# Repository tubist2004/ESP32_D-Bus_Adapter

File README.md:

# ESP32 D-Bus Adapter

This is a repository for building a (or more) ESP32 based D-Bus Adapter for BSH appliances.

It is based on the awesome work of [@hn](https://github.com/hn) who did reverse engineering of the protocol, wrote some software and most important: Talked about it!

Please follow his project: https://github.com/hn/bsh-home-appliances

And see his talk at the 39C3: https://media.ccc.de/v/39c3-hacking-washing-machines

---

<a href="https://github.com/tubist2004/ESP32_D-Bus_Adapter">ESP32_D-Bus_Adapter</a> © 2026 by <a href="https://example.com">tubist2004</a> is licensed under <a href="https://creativecommons.org/licenses/by/4.0/">CC BY 4.0</a>

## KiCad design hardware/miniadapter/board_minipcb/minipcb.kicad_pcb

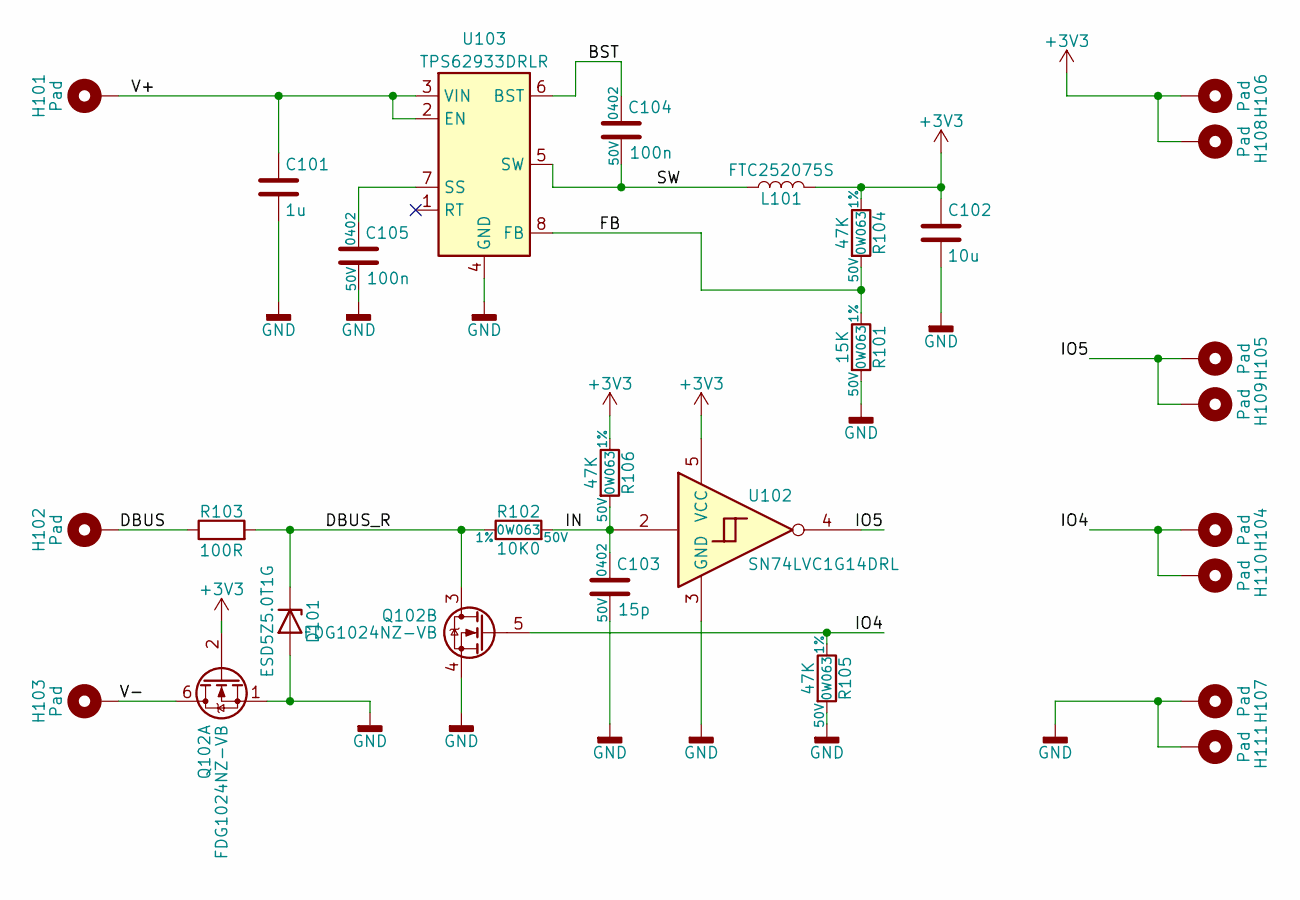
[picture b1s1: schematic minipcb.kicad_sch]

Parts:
C101: 1u; C_0603_1608Metric
C102: 10u; C_0603_1608Metric
C103: C_15p_0402_NP0_5%_50V; C_0402_1005Metric; Tolerance 5%; Voltage 50V
C104, C105: C_100n_0402_X7R_10%_50V; C_0402_1005Metric; Tolerance 10%; Voltage 50V
D101: ESD5Z5.0T1G; D_SOD-523
H101, H102, H103: Pad; TE_2040852-1
H104, H105, H106, H107, H108, H109, H110, H111: Pad; SolderWirePad_1x01_SMD_1.5x3mm
L101: FTC252075S; L_Changjiang_FTC252075S
Q102: FDG1024NZ-VB; SOT-363_SC-70-6
R101: R_15K_0402_0W063_1%_100PPM_50V; R_0402_1005Metric; Tolerance 1%; Voltage 50V
R102: R_10K0_0402_0W063_1%_100PPM_50V; R_0402_1005Metric; Tolerance 1%; Voltage 50V
R103: 100R; R_0603_1608Metric
R104, R105, R106: R_47K_0402_0W063_1%_100PPM_50V; R_0402_1005Metric; Tolerance 1%; Voltage 50V
U102: SN74LVC1G14DRL; SOT-553
U103: TPS62933DRLR; SOT-583-8

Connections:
+3V3: C102.1, H106.1, H108.1, L101.2, Q102.2 (G), R104.1, R106.1, U102.5 (VCC)
/BST: C104.1, U103.6 (BST)
/DBUS: H102.1, R103.1
/DBUS_R: D101.1 (K), Q102.3 (D), R102.1, R103.2
/FB: R101.1, R104.2, U103.8 (FB)
/IN: C103.1, R102.2, R106.2, U102.2
/IO4: H104.1, H110.1, Q102.5 (G), R105.1
/IO5: H105.1, H109.1, U102.4
/SW: C104.2, L101.1, U103.5 (SW)
/V+: C101.1, H101.1, U103.2 (EN), U103.3 (VIN)
/V-: H103.1, Q102.6 (D)
GND: C101.2, C102.2, C103.2, C105.2, D101.2 (A), H107.1, H111.1, Q102.1 (S), Q102.4 (S), R101.2, R105.2, U102.3 (GND), U103.4 (GND)
unnamed: C105.1, U103.7 (SS)

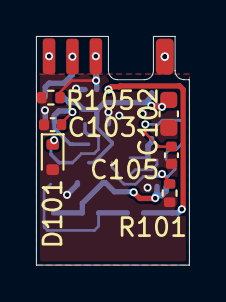
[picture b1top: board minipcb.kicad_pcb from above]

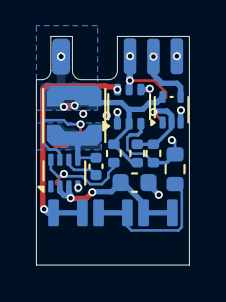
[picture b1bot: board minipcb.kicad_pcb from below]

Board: 2 copper layers, 8.5 x 12.7 mm, 27 parts (17 on the bottom side), 13 nets.

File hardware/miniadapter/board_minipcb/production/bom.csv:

Designator,Footprint,Quantity,Value,LCSC Part #
C101,0603,1,1u,
C102,0603,1,10u,
C103,0402,1,C_15p_0402_NP0_5%_50V,
"C104, C105",0402,2,C_100n_0402_X7R_10%_50V,
D101,D_SOD-523,1,ESD5Z5.0T1G,
"H101, H102, H103",TE_2040852-1,3,Pad,
L101,L_Coilcraft_LPS3010,1,FTC252075S,
Q102,SOT-363_SC-70-6,1,FDG1024NZ-VB,
R101,0402,1,R_15K_0402_0W063_1%_100PPM_50V,
R102,0402,1,R_10K0_0402_0W063_1%_100PPM_50V,
R103,0603,1,100R,
"R104, R105, R106",0402,3,R_47K_0402_0W063_1%_100PPM_50V,
U102,SOT-553,1,SN74LVC1G14DRL,
U103,SOT-583-8,1,TPS62933DRLR,

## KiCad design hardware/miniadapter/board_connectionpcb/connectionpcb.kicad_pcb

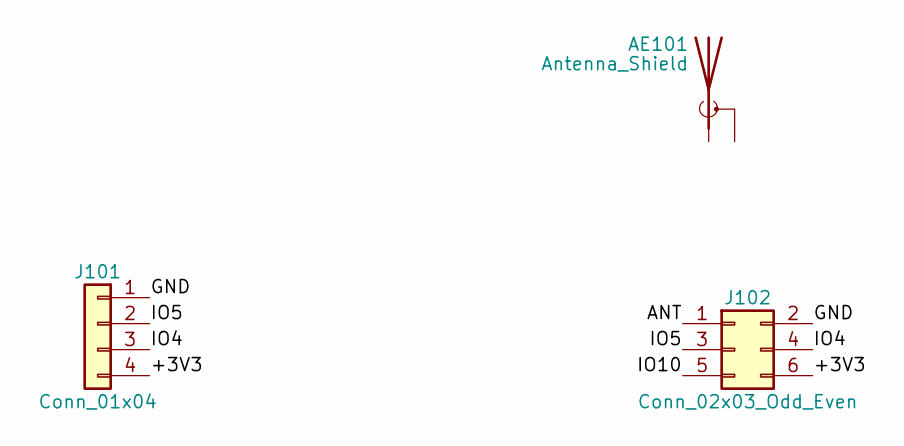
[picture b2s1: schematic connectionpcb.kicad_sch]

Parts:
AE101: Antenna_Shield; Johanson_2450AT18x100_2400-2500Mhz
J101: Conn_01x04; minipcb_alt_boardedge
J102: Conn_02x03_Odd_Even; ESP8685-WROOM-07

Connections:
/+3V3: J101.4, J102.6
/ANT: J102.1
/GND: J101.1, J102.2
/IO4: J101.3, J102.4
/IO5: J101.2, J102.3
/IO10: J102.5

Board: 2 copper layers, 3 parts (1 on the bottom side), 4 nets.

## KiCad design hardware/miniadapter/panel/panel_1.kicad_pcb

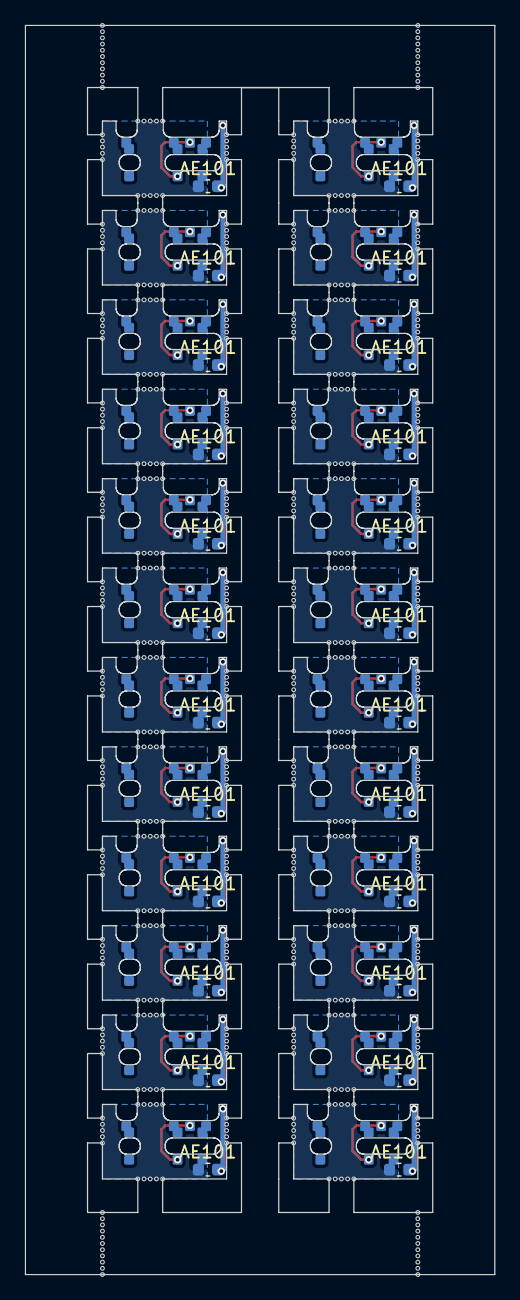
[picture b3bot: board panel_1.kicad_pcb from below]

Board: 2 copper layers, 37.8 x 100.6 mm, 596 parts (24 on the bottom side), 96 nets.

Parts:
AE101, AE101#2, AE101#3, AE101#4, AE101#5, AE101#6, AE101#7, AE101#8, AE101#9, AE101#10, AE101#11, AE101#12, AE101#13, AE101#14, AE101#15, AE101#16, AE101#17, AE101#18, AE101#19, AE101#20, AE101#21, AE101#22, AE101#23, AE101#24: Antenna_Shield; C_0603_1608Metric
J101, J101#2, J101#3, J101#4, J101#5, J101#6, J101#7, J101#8, J101#9, J101#10, J101#11, J101#12, J101#13, J101#14, J101#15, J101#16, J101#17, J101#18, J101#19, J101#20, J101#21, J101#22, J101#23, J101#24: Conn_01x04; minipcb_alt_boardedge
J102, J102#2, J102#3, J102#4, J102#5, J102#6, J102#7, J102#8, J102#9, J102#10, J102#11, J102#12, J102#13, J102#14, J102#15, J102#16, J102#17, J102#18, J102#19, J102#20, J102#21, J102#22, J102#23, J102#24: Conn_02x03_Odd_Even; ESP8685-WROOM-07
KiKit_MB_1_1, KiKit_MB_1_2, KiKit_MB_1_3, KiKit_MB_1_4, KiKit_MB_1_5, KiKit_MB_2_1, KiKit_MB_2_2, KiKit_MB_2_3, KiKit_MB_2_4, KiKit_MB_2_5, KiKit_MB_3_1, KiKit_MB_3_2, KiKit_MB_3_3, KiKit_MB_3_4, KiKit_MB_3_5, KiKit_MB_4_1, KiKit_MB_4_2, KiKit_MB_4_3, KiKit_MB_4_4, KiKit_MB_4_5, KiKit_MB_5_1, KiKit_MB_5_2, KiKit_MB_5_3, KiKit_MB_5_4, KiKit_MB_5_5, KiKit_MB_6_1, KiKit_MB_6_2, KiKit_MB_6_3, KiKit_MB_6_4, KiKit_MB_6_5, KiKit_MB_7_1, KiKit_MB_7_2, KiKit_MB_7_3, KiKit_MB_7_4, KiKit_MB_7_5, KiKit_MB_8_1, KiKit_MB_8_2, KiKit_MB_8_3, KiKit_MB_8_4, KiKit_MB_8_5, KiKit_MB_9_1, KiKit_MB_9_2, KiKit_MB_9_3, KiKit_MB_9_4, KiKit_MB_9_5, KiKit_MB_10_1, KiKit_MB_10_2, KiKit_MB_10_3, KiKit_MB_10_4, KiKit_MB_10_5, KiKit_MB_11_1, KiKit_MB_11_2, KiKit_MB_11_3, KiKit_MB_11_4, KiKit_MB_11_5, KiKit_MB_12_1, KiKit_MB_12_2, KiKit_MB_12_3, KiKit_MB_12_4, KiKit_MB_12_5, KiKit_MB_13_1, KiKit_MB_13_2, KiKit_MB_13_3, KiKit_MB_13_4, KiKit_MB_13_5, KiKit_MB_14_1, KiKit_MB_14_2, KiKit_MB_14_3, KiKit_MB_14_4, KiKit_MB_14_5, KiKit_MB_15_1, KiKit_MB_15_2, KiKit_MB_15_3, KiKit_MB_15_4, KiKit_MB_15_5, KiKit_MB_16_1, KiKit_MB_16_2, KiKit_MB_16_3, KiKit_MB_16_4, KiKit_MB_16_5, KiKit_MB_17_1, KiKit_MB_17_2, KiKit_MB_17_3, KiKit_MB_17_4, KiKit_MB_17_5, KiKit_MB_18_1, KiKit_MB_18_2, KiKit_MB_18_3, KiKit_MB_18_4, KiKit_MB_18_5, KiKit_MB_19_1, KiKit_MB_19_2, KiKit_MB_19_3, KiKit_MB_19_4, KiKit_MB_19_5, KiKit_MB_20_1, KiKit_MB_20_2, KiKit_MB_20_3, KiKit_MB_20_4, KiKit_MB_20_5, KiKit_MB_21_1, KiKit_MB_21_2, KiKit_MB_21_3, KiKit_MB_21_4, KiKit_MB_21_5, KiKit_MB_22_1, KiKit_MB_22_2, KiKit_MB_22_3, KiKit_MB_22_4, KiKit_MB_22_5, KiKit_MB_23_1, KiKit_MB_23_2, KiKit_MB_23_3, KiKit_MB_23_4, KiKit_MB_23_5, KiKit_MB_24_1, KiKit_MB_24_2, KiKit_MB_24_3, KiKit_MB_24_4, KiKit_MB_24_5, KiKit_MB_25_1, KiKit_MB_25_2, KiKit_MB_25_3, KiKit_MB_25_4, KiKit_MB_25_5, KiKit_MB_26_1, KiKit_MB_26_2, KiKit_MB_26_3, KiKit_MB_26_4, KiKit_MB_26_5, KiKit_MB_27_1, KiKit_MB_27_2, KiKit_MB_27_3, KiKit_MB_27_4, KiKit_MB_27_5, KiKit_MB_28_1, KiKit_MB_28_2, KiKit_MB_28_3, KiKit_MB_28_4, KiKit_MB_28_5, KiKit_MB_29_1, KiKit_MB_29_2, KiKit_MB_29_3, KiKit_MB_29_4, KiKit_MB_29_5, KiKit_MB_30_1, KiKit_MB_30_2, KiKit_MB_30_3, KiKit_MB_30_4, KiKit_MB_30_5, KiKit_MB_31_1, KiKit_MB_31_2, KiKit_MB_31_3, KiKit_MB_31_4, KiKit_MB_31_5, KiKit_MB_32_1, KiKit_MB_32_2, KiKit_MB_32_3, KiKit_MB_32_4, KiKit_MB_32_5, KiKit_MB_33_1, KiKit_MB_33_2, KiKit_MB_33_3, KiKit_MB_33_4, KiKit_MB_33_5, KiKit_MB_34_1, KiKit_MB_34_2, KiKit_MB_34_3, KiKit_MB_34_4, KiKit_MB_34_5, KiKit_MB_35_1, KiKit_MB_35_2, KiKit_MB_35_3, KiKit_MB_35_4, KiKit_MB_35_5, KiKit_MB_36_1, KiKit_MB_36_2, KiKit_MB_36_3, KiKit_MB_36_4, KiKit_MB_36_5, KiKit_MB_37_1, KiKit_MB_37_2, KiKit_MB_37_3, KiKit_MB_37_4, KiKit_MB_37_5, KiKit_MB_38_1, KiKit_MB_38_2, KiKit_MB_38_3, KiKit_MB_38_4, KiKit_MB_38_5, KiKit_MB_39_1, KiKit_MB_39_2, KiKit_MB_39_3, KiKit_MB_39_4, KiKit_MB_39_5, KiKit_MB_40_1, KiKit_MB_40_2, KiKit_MB_40_3, KiKit_MB_40_4, KiKit_MB_40_5, KiKit_MB_41_1, KiKit_MB_41_2, KiKit_MB_41_3, KiKit_MB_41_4, KiKit_MB_41_5, KiKit_MB_42_1, KiKit_MB_42_2, KiKit_MB_42_3, KiKit_MB_42_4, KiKit_MB_42_5, KiKit_MB_43_1, KiKit_MB_43_2, KiKit_MB_43_3, KiKit_MB_43_4, KiKit_MB_43_5, KiKit_MB_44_1, KiKit_MB_44_2, KiKit_MB_44_3, KiKit_MB_44_4, KiKit_MB_44_5, KiKit_MB_45_1, KiKit_MB_45_2, KiKit_MB_45_3, KiKit_MB_45_4, KiKit_MB_45_5, KiKit_MB_46_1, KiKit_MB_46_2, KiKit_MB_46_3, KiKit_MB_46_4, KiKit_MB_46_5, KiKit_MB_47_1, KiKit_MB_47_2, KiKit_MB_47_3, KiKit_MB_47_4, KiKit_MB_47_5, KiKit_MB_48_1, KiKit_MB_48_2, KiKit_MB_48_3, KiKit_MB_48_4, KiKit_MB_48_5, KiKit_MB_49_1, KiKit_MB_49_2, KiKit_MB_49_3, KiKit_MB_49_4, KiKit_MB_49_5, KiKit_MB_50_1, KiKit_MB_50_2, KiKit_MB_50_3, KiKit_MB_50_4, KiKit_MB_50_5, KiKit_MB_51_1, KiKit_MB_51_2, KiKit_MB_51_3, KiKit_MB_51_4, KiKit_MB_51_5, KiKit_MB_52_1, KiKit_MB_52_2, KiKit_MB_52_3, KiKit_MB_52_4, KiKit_MB_52_5, KiKit_MB_53_1, KiKit_MB_53_2, KiKit_MB_53_3, KiKit_MB_53_4, KiKit_MB_53_5, KiKit_MB_54_1, KiKit_MB_54_2, KiKit_MB_54_3, KiKit_MB_54_4, KiKit_MB_54_5, KiKit_MB_55_1, KiKit_MB_55_2, KiKit_MB_55_3, KiKit_MB_55_4, KiKit_MB_55_5, KiKit_MB_56_1, KiKit_MB_56_2, KiKit_MB_56_3, KiKit_MB_56_4, KiKit_MB_56_5, KiKit_MB_57_1, KiKit_MB_57_2, KiKit_MB_57_3, KiKit_MB_57_4, KiKit_MB_57_5, KiKit_MB_58_1, KiKit_MB_58_2, KiKit_MB_58_3, KiKit_MB_58_4, KiKit_MB_58_5, KiKit_MB_59_1, KiKit_MB_59_2, KiKit_MB_59_3, KiKit_MB_59_4, KiKit_MB_59_5, KiKit_MB_60_1, KiKit_MB_60_2, KiKit_MB_60_3, KiKit_MB_60_4, KiKit_MB_60_5, KiKit_MB_61_1, KiKit_MB_61_2, KiKit_MB_61_3, KiKit_MB_61_4, KiKit_MB_61_5, KiKit_MB_62_1, KiKit_MB_62_2, KiKit_MB_62_3, KiKit_MB_62_4, KiKit_MB_62_5, KiKit_MB_63_1, KiKit_MB_63_2, KiKit_MB_63_3, KiKit_MB_63_4, KiKit_MB_63_5, KiKit_MB_64_1, KiKit_MB_64_2, KiKit_MB_64_3, KiKit_MB_64_4, KiKit_MB_64_5, KiKit_MB_65_1, KiKit_MB_65_2, KiKit_MB_65_3, KiKit_MB_65_4, KiKit_MB_65_5, KiKit_MB_66_1, KiKit_MB_66_2, KiKit_MB_66_3, KiKit_MB_66_4, KiKit_MB_66_5, KiKit_MB_67_1, KiKit_MB_67_2, KiKit_MB_67_3, KiKit_MB_67_4, KiKit_MB_67_5, KiKit_MB_68_1, KiKit_MB_68_2, KiKit_MB_68_3, KiKit_MB_68_4, KiKit_MB_68_5, KiKit_MB_69_1, KiKit_MB_69_2, KiKit_MB_69_3, KiKit_MB_69_4, KiKit_MB_69_5, KiKit_MB_70_1, KiKit_MB_70_2, KiKit_MB_70_3, KiKit_MB_70_4, KiKit_MB_70_5, KiKit_MB_71_1, KiKit_MB_71_2, KiKit_MB_71_3, KiKit_MB_71_4, KiKit_MB_71_5, KiKit_MB_72_1, KiKit_MB_72_2, KiKit_MB_72_3, KiKit_MB_72_4, KiKit_MB_72_5, KiKit_MB_73_1, KiKit_MB_73_2, KiKit_MB_73_3, KiKit_MB_73_4, KiKit_MB_73_5, KiKit_MB_74_1, KiKit_MB_74_2, KiKit_MB_74_3, KiKit_MB_74_4, KiKit_MB_74_5, KiKit_MB_75_1, KiKit_MB_75_2, KiKit_MB_75_3, KiKit_MB_75_4, KiKit_MB_75_5, KiKit_MB_76_1, KiKit_MB_76_2, KiKit_MB_76_3, KiKit_MB_76_4, KiKit_MB_76_5, KiKit_MB_77_1, KiKit_MB_77_2, KiKit_MB_77_3, KiKit_MB_77_4, KiKit_MB_77_5, KiKit_MB_78_1, KiKit_MB_78_2, KiKit_MB_78_3, KiKit_MB_78_4, KiKit_MB_78_5, KiKit_MB_79_1, KiKit_MB_79_2, KiKit_MB_79_3, KiKit_MB_79_4, KiKit_MB_79_5, KiKit_MB_80_1, KiKit_MB_80_2, KiKit_MB_80_3, KiKit_MB_80_4, KiKit_MB_80_5, KiKit_MB_81_1, KiKit_MB_81_2, KiKit_MB_81_3, KiKit_MB_81_4, KiKit_MB_81_5, KiKit_MB_82_1, KiKit_MB_82_2, KiKit_MB_82_3, KiKit_MB_82_4, KiKit_MB_82_5, KiKit_MB_83_1, KiKit_MB_83_2, KiKit_MB_83_3, KiKit_MB_83_4, KiKit_MB_83_5, KiKit_MB_84_1, KiKit_MB_84_2, KiKit_MB_84_3, KiKit_MB_84_4, KiKit_MB_84_5, KiKit_MB_85_1, KiKit_MB_85_2, KiKit_MB_85_3, KiKit_MB_85_4, KiKit_MB_85_5, KiKit_MB_86_1, KiKit_MB_86_2, KiKit_MB_86_3, KiKit_MB_86_4, KiKit_MB_86_5, KiKit_MB_87_1, KiKit_MB_87_2, KiKit_MB_87_3, KiKit_MB_87_4, KiKit_MB_87_5, KiKit_MB_88_1, KiKit_MB_88_2, KiKit_MB_88_3, KiKit_MB_88_4, KiKit_MB_88_5, KiKit_MB_89_1, KiKit_MB_89_2, KiKit_MB_89_3, KiKit_MB_89_4, KiKit_MB_89_5, KiKit_MB_90_1, KiKit_MB_90_2, KiKit_MB_90_3, KiKit_MB_90_4, KiKit_MB_90_5, KiKit_MB_91_1, KiKit_MB_91_2, KiKit_MB_91_3, KiKit_MB_91_4, KiKit_MB_91_5, KiKit_MB_92_1, KiKit_MB_92_2, KiKit_MB_92_3, KiKit_MB_92_4, KiKit_MB_92_5, KiKit_MB_93_1, KiKit_MB_93_2, KiKit_MB_93_3, KiKit_MB_93_4, KiKit_MB_93_5, KiKit_MB_94_1, KiKit_MB_94_2, KiKit_MB_94_3, KiKit_MB_94_4, KiKit_MB_94_5, KiKit_MB_95_1, KiKit_MB_95_2, KiKit_MB_95_3, KiKit_MB_95_4, KiKit_MB_95_5, KiKit_MB_96_1, KiKit_MB_96_2, KiKit_MB_96_3, KiKit_MB_96_4, KiKit_MB_96_5, KiKit_MB_97_1, KiKit_MB_97_2, KiKit_MB_97_3, KiKit_MB_97_4, KiKit_MB_97_5, KiKit_MB_97_6, KiKit_MB_97_7, KiKit_MB_97_8, KiKit_MB_97_9, KiKit_MB_97_10, KiKit_MB_97_11, KiKit_MB_98_1, KiKit_MB_98_2, KiKit_MB_98_3, KiKit_MB_98_4, KiKit_MB_98_5, KiKit_MB_98_6, KiKit_MB_98_7, KiKit_MB_98_8, KiKit_MB_98_9, KiKit_MB_98_10, KiKit_MB_98_11, KiKit_MB_99_1, KiKit_MB_99_2, KiKit_MB_99_3, KiKit_MB_99_4, KiKit_MB_99_5, KiKit_MB_99_6, KiKit_MB_99_7, KiKit_MB_99_8, KiKit_MB_99_9, KiKit_MB_99_10, KiKit_MB_99_11, KiKit_MB_100_1, KiKit_MB_100_2, KiKit_MB_100_3, KiKit_MB_100_4, KiKit_MB_100_5, KiKit_MB_100_6, KiKit_MB_100_7, KiKit_MB_100_8, KiKit_MB_100_9, KiKit_MB_100_10, KiKit_MB_100_11: NPTH

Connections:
Board_0-/+3V3: J101#3.4, J102#4.6
Board_0-/GND: J101#3.1, J102#4.2
Board_0-/IO4: J101#3.3, J102#4.4
Board_0-/IO5: J101#3.2, J102#4.3
Board_1-/+3V3: J101#7.4, J102#3.6
Board_1-/GND: J101#7.1, J102#3.2
Board_1-/IO4: J101#7.3, J102#3.4
Board_1-/IO5: J101#7.2, J102#3.3
Board_2-/+3V3: J101#17.4, J102#18.6
Board_2-/GND: J101#17.1, J102#18.2
Board_2-/IO4: J101#17.3, J102#18.4
Board_2-/IO5: J101#17.2, J102#18.3
Board_3-/+3V3: J101#21.4, J102#5.6
Board_3-/GND: J101#21.1, J102#5.2
Board_3-/IO4: J101#21.3, J102#5.4
Board_3-/IO5: J101#21.2, J102#5.3
Board_4-/+3V3: J101#18.4, J102#21.6
Board_4-/GND: J101#18.1, J102#21.2
Board_4-/IO4: J101#18.3, J102#21.4
Board_4-/IO5: J101#18.2, J102#21.3
Board_5-/+3V3: J101#20.4, J102#7.6
Board_5-/GND: J101#20.1, J102#7.2
Board_5-/IO4: J101#20.3, J102#7.4
Board_5-/IO5: J101#20.2, J102#7.3
Board_6-/+3V3: J101#23.4, J102#13.6
Board_6-/GND: J101#23.1, J102#13.2
Board_6-/IO4: J101#23.3, J102#13.4
Board_6-/IO5: J101#23.2, J102#13.3
Board_7-/+3V3: J101#8.4, J102#2.6
Board_7-/GND: J101#8.1, J102#2.2
Board_7-/IO4: J101#8.3, J102#2.4
Board_7-/IO5: J101#8.2, J102#2.3
Board_8-/+3V3: J101#6.4, J102#19.6
Board_8-/GND: J101#6.1, J102#19.2
Board_8-/IO4: J101#6.3, J102#19.4
Board_8-/IO5: J101#6.2, J102#19.3
Board_9-/+3V3: J101#16.4, J102#15.6
Board_9-/GND: J101#16.1, J102#15.2
Board_9-/IO4: J101#16.3, J102#15.4
Board_9-/IO5: J101#16.2, J102#15.3
Board_10-/+3V3: J101#5.4, J102.6
Board_10-/GND: J101#5.1, J102.2
Board_10-/IO4: J101#5.3, J102.4
Board_10-/IO5: J101#5.2, J102.3
Board_11-/+3V3: J101#24.4, J102#22.6
Board_11-/GND: J101#24.1, J102#22.2
Board_11-/IO4: J101#24.3, J102#22.4
Board_11-/IO5: J101#24.2, J102#22.3
Board_12-/+3V3: J101#12.4, J102#10.6
Board_12-/GND: J101#12.1, J102#10.2
Board_12-/IO4: J101#12.3, J102#10.4
Board_12-/IO5: J101#12.2, J102#10.3
Board_13-/+3V3: J101.4, J102#14.6
Board_13-/GND: J101.1, J102#14.2
Board_13-/IO4: J101.3, J102#14.4
Board_13-/IO5: J101.2, J102#14.3
Board_14-/+3V3: J101#13.4, J102#11.6
Board_14-/GND: J101#13.1, J102#11.2
Board_14-/IO4: J101#13.3, J102#11.4
Board_14-/IO5: J101#13.2, J102#11.3
Board_15-/+3V3: J101#15.4, J102#17.6
Board_15-/GND: J101#15.1, J102#17.2
Board_15-/IO4: J101#15.3, J102#17.4
Board_15-/IO5: J101#15.2, J102#17.3
Board_16-/+3V3: J101#19.4, J102#16.6
Board_16-/GND: J101#19.1, J102#16.2
Board_16-/IO4: J101#19.3, J102#16.4
Board_16-/IO5: J101#19.2, J102#16.3
Board_17-/+3V3: J101#4.4, J102#9.6
Board_17-/GND: J101#4.1, J102#9.2
Board_17-/IO4: J101#4.3, J102#9.4
Board_17-/IO5: J101#4.2, J102#9.3
Board_18-/+3V3: J101#22.4, J102#6.6
Board_18-/GND: J101#22.1, J102#6.2
Board_18-/IO4: J101#22.3, J102#6.4
Board_18-/IO5: J101#22.2, J102#6.3
Board_19-/+3V3: J101#9.4, J102#23.6
Board_19-/GND: J101#9.1, J102#23.2
Board_19-/IO4: J101#9.3, J102#23.4
Board_19-/IO5: J101#9.2, J102#23.3
Board_20-/+3V3: J101#14.4, J102#24.6
Board_20-/GND: J101#14.1, J102#24.2
Board_20-/IO4: J101#14.3, J102#24.4
Board_20-/IO5: J101#14.2, J102#24.3
Board_21-/+3V3: J101#2.4, J102#20.6
Board_21-/GND: J101#2.1, J102#20.2
Board_21-/IO4: J101#2.3, J102#20.4
Board_21-/IO5: J101#2.2, J102#20.3
Board_22-/+3V3: J101#10.4, J102#8.6
Board_22-/GND: J101#10.1, J102#8.2
Board_22-/IO4: J101#10.3, J102#8.4
Board_22-/IO5: J101#10.2, J102#8.3
Board_23-/+3V3: J101#11.4, J102#12.6
Board_23-/GND: J101#11.1, J102#12.2
Board_23-/IO4: J101#11.3, J102#12.4
Board_23-/IO5: J101#11.2, J102#12.3

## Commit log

2026-01-05 First layout done
2026-01-05 Fix README formatting and update title
2026-01-08 new layout
2026-01-17 layout changes and panel generation
2026-01-17 production files generated
2026-01-17 top layer changes minipcb
